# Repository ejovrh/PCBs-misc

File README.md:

# PCBs-misc
breakout stuff

breakout boards for all kinds of stull i currently need

- nikon d700 10-pin connector
- TPS63031 3.3v buck/boost dcdc converter
-

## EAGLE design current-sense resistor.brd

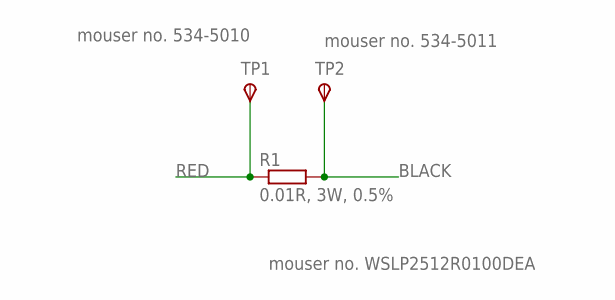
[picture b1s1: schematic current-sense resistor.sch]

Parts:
R1: 0.01R, 3W, 0.5%; R2512
TP1: 534-5011; P1-20
TP2: 534-5010; P1-20

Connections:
BLACK: R1.2, TP2.TP
RED: R1.1, TP1.TP

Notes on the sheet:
mouser no. 534-5011
mouser no. 534-5010
mouser no. WSLP2512R0100DEA

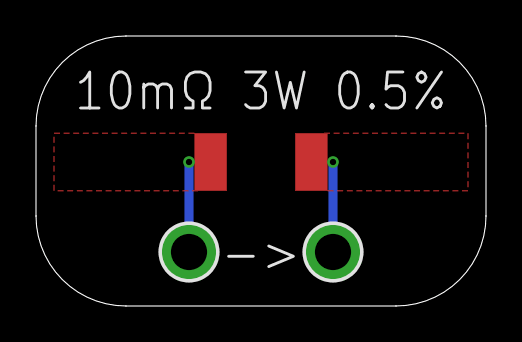
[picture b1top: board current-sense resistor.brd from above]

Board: 2 copper layers, 25.0 x 15.0 mm, 3 parts (0 on the bottom side), 2 nets.

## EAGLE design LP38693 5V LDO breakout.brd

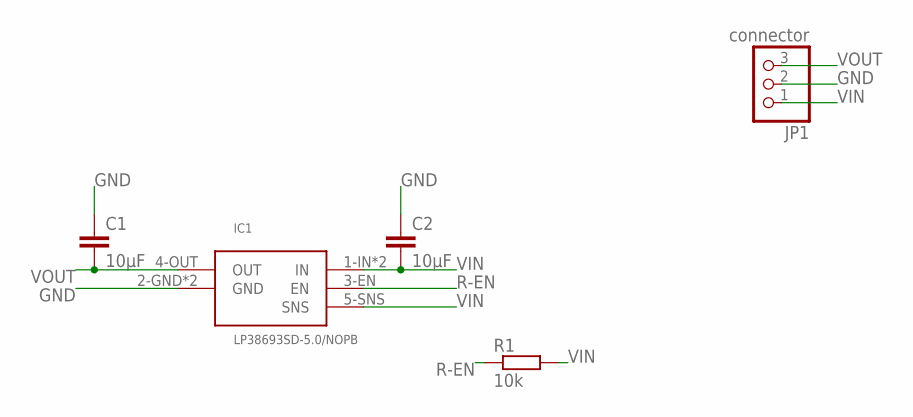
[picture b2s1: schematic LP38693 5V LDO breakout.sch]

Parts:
C1, C2: 10μF; C0402
IC1: LP38693SD-5.0/NOPB; WSON6
JP1: connector; 1X03
R1: 10k; R0402

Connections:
GND: C1.1, C2.1, IC1.2-GND (GND), IC1.GND1 (GND), JP1.2
R-EN: IC1.3-EN (EN), R1.1
VIN: C2.2, IC1.1-IN (IN), IC1.5-SNS (SNS), IC1.6-IN (IN), JP1.1, R1.2
VOUT: C1.2, IC1.4-OUT (OUT), JP1.3

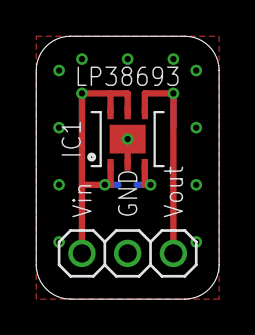
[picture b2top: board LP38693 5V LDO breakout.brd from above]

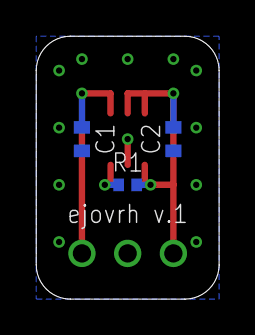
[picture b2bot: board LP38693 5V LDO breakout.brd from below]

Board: 2 copper layers, 10.2 x 14.6 mm, 5 parts (3 on the bottom side), 4 nets.

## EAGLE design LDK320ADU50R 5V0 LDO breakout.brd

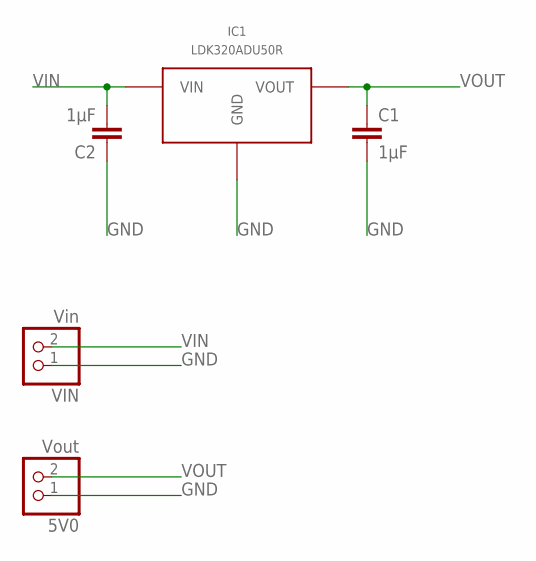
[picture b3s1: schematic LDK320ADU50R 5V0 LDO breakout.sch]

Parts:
5V0: Vout; 1X02
C1, C2: 1μF; C0402
IC1: LDK320ADU50R; SOT-89-D
VIN: Vin; 1X02

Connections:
GND: 5V0.1, C1.2, C2.1, IC1.GND, VIN.1
VIN: C2.2, IC1.VIN, VIN.2
VOUT: 5V0.2, C1.1, IC1.VOUT

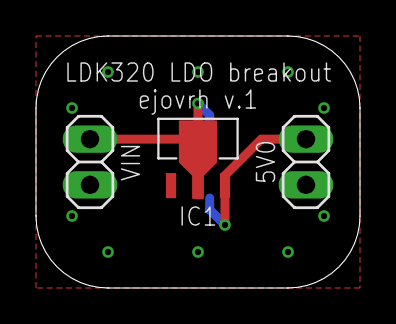
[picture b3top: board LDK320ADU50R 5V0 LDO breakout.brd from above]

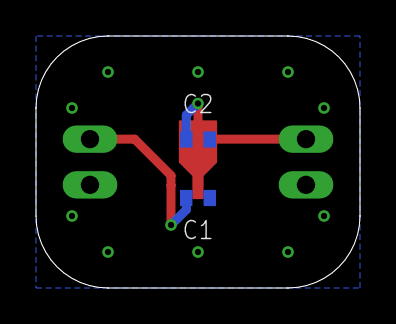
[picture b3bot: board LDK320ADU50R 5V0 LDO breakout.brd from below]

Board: 2 copper layers, 18.0 x 14.0 mm, 5 parts (2 on the bottom side), 3 nets.

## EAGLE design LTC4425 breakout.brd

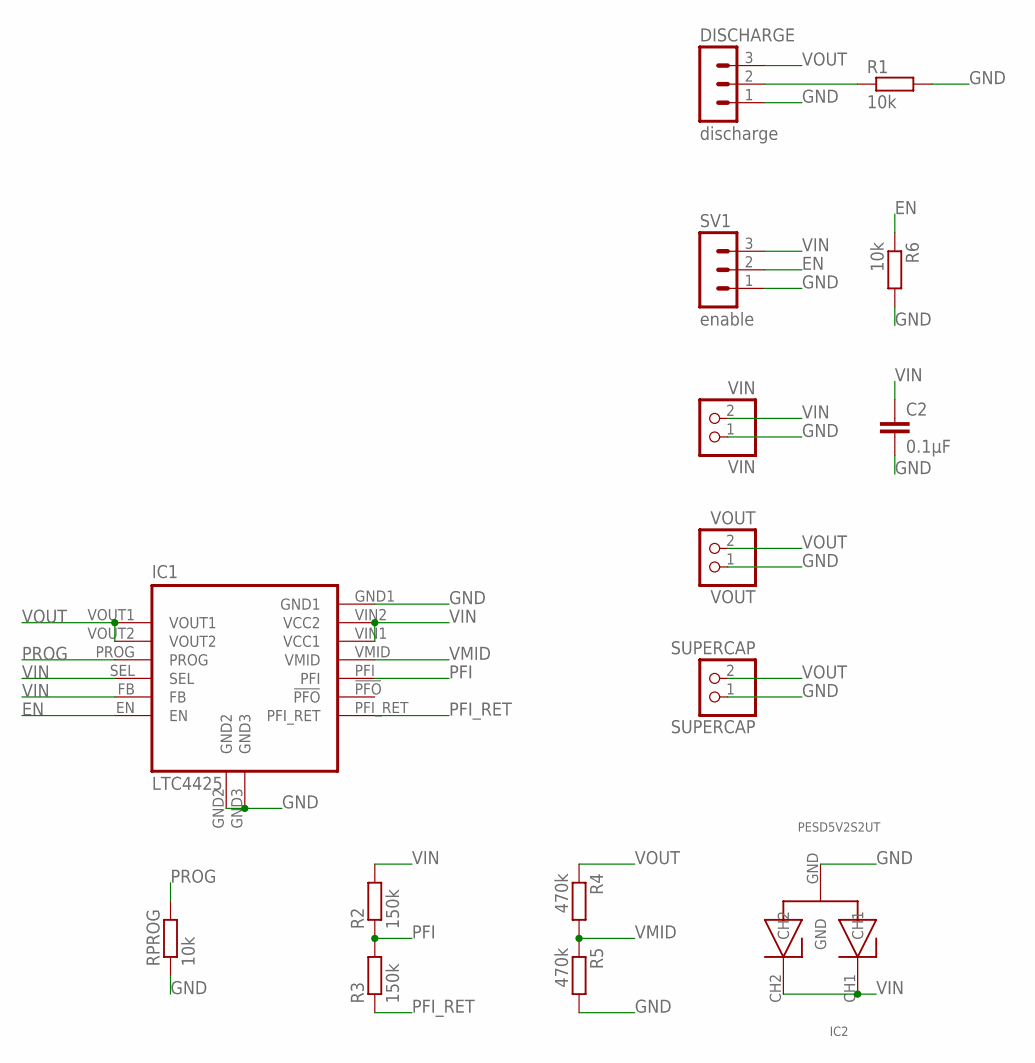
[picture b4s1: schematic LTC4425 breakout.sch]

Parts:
C2: 0.1µF; C0805
DISCHARGE: discharge; MA03-1
IC1: LTC4425; MSOP
IC2: PESD5V2S2UT; SOT-23
R1: 10k; R1206
R2, R3: 150k; R0805
R4, R5: 470k; R0805
R6: 10k; R0805
RPROG: 10k; R1206
SUPERCAP: SUPERCAP; 1X02
SV1: enable; MA03-1
VIN: VIN; 1X02
VOUT: VOUT; 1X02

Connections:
EN: IC1.EN, R6.1, SV1.2
GND: C2.2, DISCHARGE.1, IC1.GND1, IC1.GND2, IC1.GND3, IC2.GND, R1.2, R5.2, R6.2, RPROG.1, SUPERCAP.1, SV1.1, VIN.1, VOUT.1
unnamed: DISCHARGE.2, R1.1
PFI: IC1.PFI, R2.1, R3.2
PFI_RET: IC1.PFI_RET, R3.1
PROG: IC1.PROG, RPROG.2
VIN: C2.1, IC1.FB, IC1.SEL, IC1.VIN1 (VCC1), IC1.VIN2 (VCC2), IC2.CH1, IC2.CH2, R2.2, SV1.3, VIN.2
VMID: IC1.VMID, R4.2, R5.1
VOUT: DISCHARGE.3, IC1.VOUT1, IC1.VOUT2, R4.1, SUPERCAP.2, VOUT.2

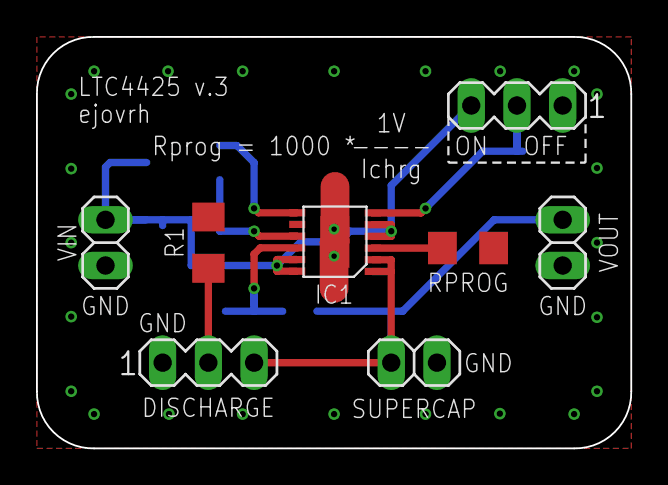
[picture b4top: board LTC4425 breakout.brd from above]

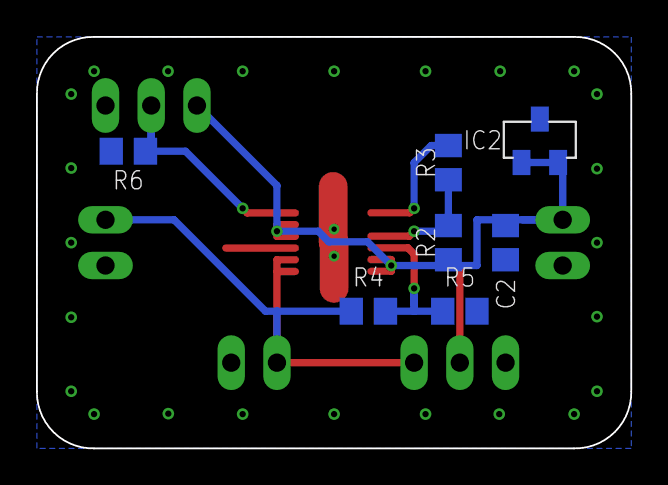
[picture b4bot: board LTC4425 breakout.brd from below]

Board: 2 copper layers, 33.0 x 22.9 mm, 15 parts (7 on the bottom side), 9 nets.

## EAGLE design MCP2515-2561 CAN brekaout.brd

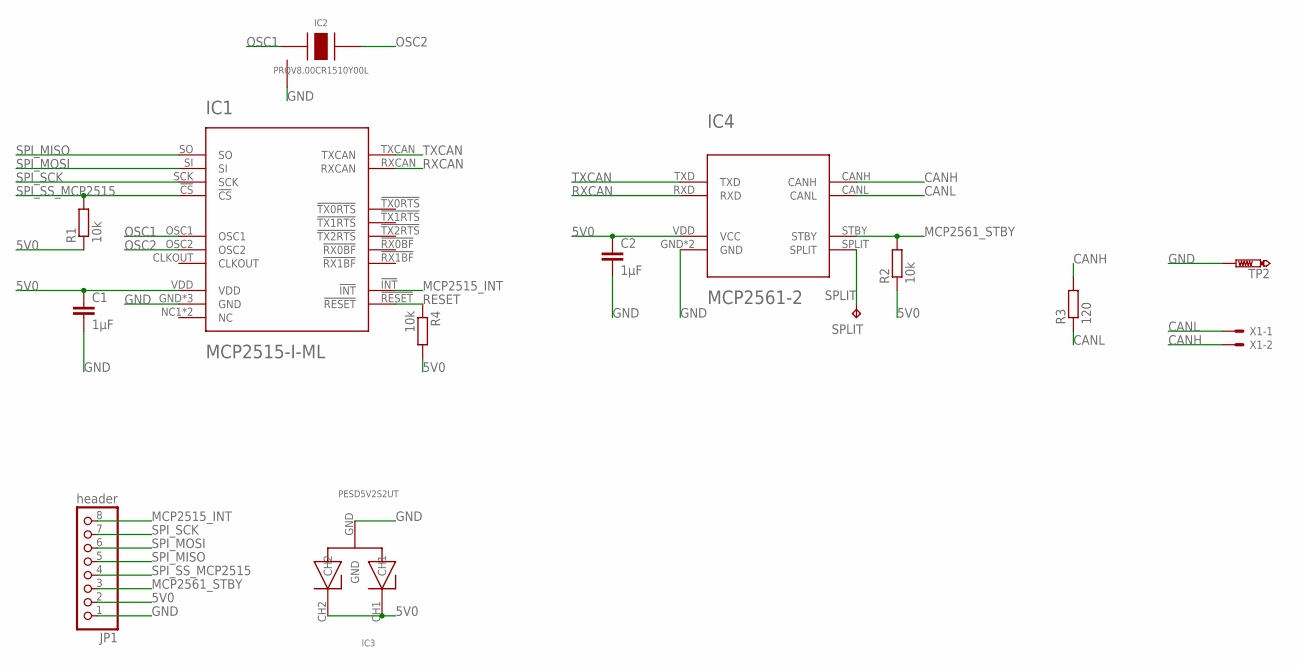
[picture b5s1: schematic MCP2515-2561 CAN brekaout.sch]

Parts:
C1, C2: 1μF; C0402
IC1: MCP2515-I-ML; QFN20
IC2: PRQV8.00CR1510Y00L; SMT
IC3: PESD5V2S2UT; SOT-23
IC4: MCP2561-2; DFN10
JP1: header; 1X08
R1, R2, R4: 10k; R0402
R3: 120; R0805
SPLIT: TPB2,54; B2,54
TP2: PTR1PAD1-13Y; P1-13Y
X1: 22-23-2021

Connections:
5V0: C1.1, C2.1, IC1.VDD, IC3.CH1, IC3.CH2, IC4.VDD (VCC), JP1.2, R1.1, R2.1, R4.2
CANH: IC4.CANH, R3.2, X1.2
CANL: IC4.CANL, R3.1, X1.1
GND: C1.2, C2.2, IC1.GND, IC1.GND1 (GND), IC1.GND6 (GND), IC2.GND, IC3.GND, IC4.GND, IC4.VSS (GND), JP1.1, TP2.TP
MCP2515_INT: IC1.!INT!, JP1.8
MCP2561_STBY: IC4.STBY, JP1.3, R2.2
OSC1: IC1.OSC1, IC2.XTAL1
OSC2: IC1.OSC2, IC2.XTAL2
RESET: IC1.!RESET!, R4.1
RXCAN: IC1.RXCAN, IC4.RXD
SPI_MISO: IC1.SO, JP1.5
SPI_MOSI: IC1.SI, JP1.6
SPI_SCK: IC1.SCK, JP1.7
SPI_SS_MCP2515: IC1.!CS!, JP1.4, R1.2
SPLIT: IC4.SPLIT, SPLIT.TP
TXCAN: IC1.TXCAN, IC4.TXD

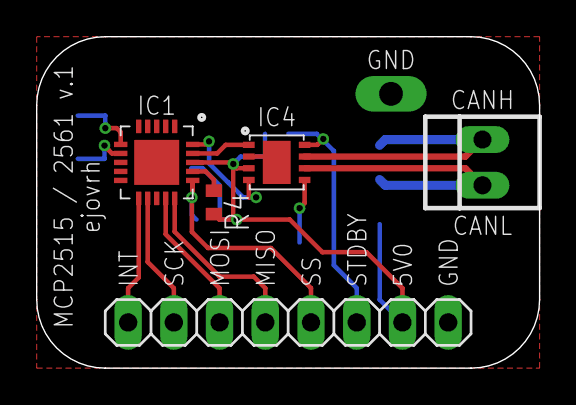
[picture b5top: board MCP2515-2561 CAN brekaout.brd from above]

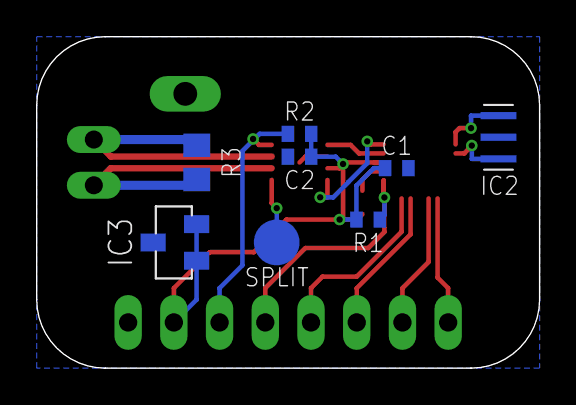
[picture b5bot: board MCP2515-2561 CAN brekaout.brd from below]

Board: 2 copper layers, 27.9 x 18.4 mm, 14 parts (8 on the bottom side), 16 nets.

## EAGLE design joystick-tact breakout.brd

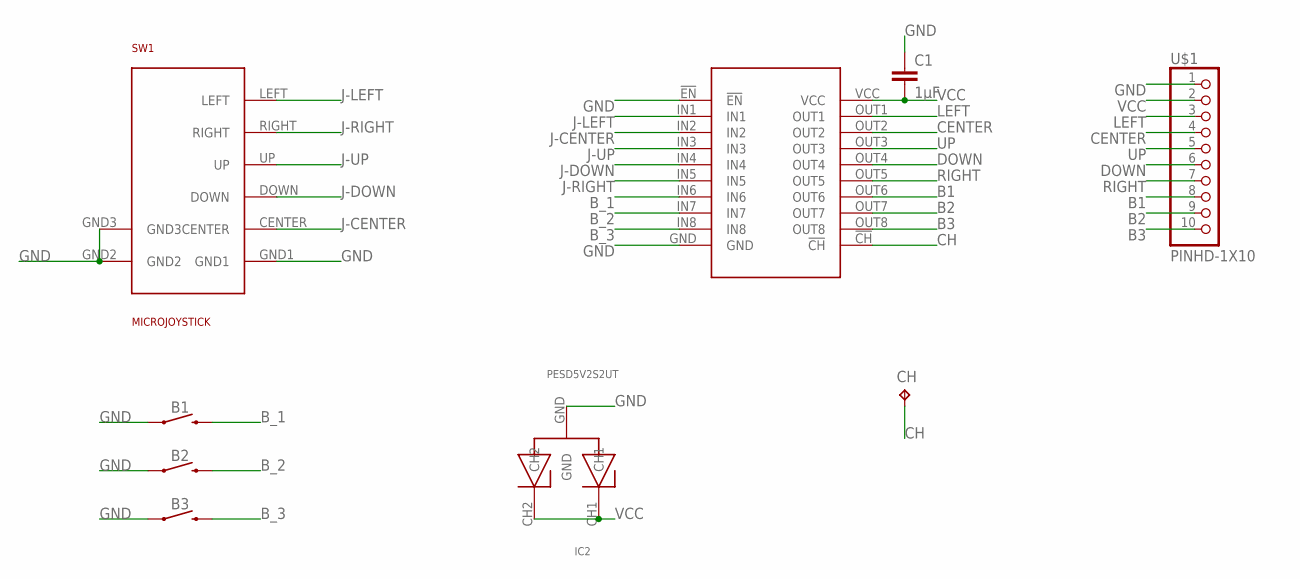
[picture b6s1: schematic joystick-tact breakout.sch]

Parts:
B1, B2, B3: MOMENTARY-SWITCH-SPST-SMD-4.5MM; TACTILE_SWITCH_SMD_4.5MM
C1: 1μF; C0805
CH: TPB2,54; B2,54
IC1: MAX6818; TSSOP20
IC2: PESD5V2S2UT; SOT-23
SW1: MICROJOYSTICK
U$1: PINHD-1X10; 1X10-BIG

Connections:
B1: IC1.OUT6, U$1.8
B2: IC1.OUT7, U$1.9
B3: IC1.OUT8, U$1.10
B_1: B1.1 (2), B1.4 (2), IC1.IN6
B_2: B2.1 (2), B2.4 (2), IC1.IN7
B_3: B3.1 (2), B3.4 (2), IC1.IN8
CENTER: IC1.OUT2, U$1.4
CH: CH.TP, IC1.!CH!
DOWN: IC1.OUT4, U$1.6
GND: B1.2 (1), B1.3 (1), B2.2 (1), B2.3 (1), B3.2 (1), B3.3 (1), C1.1, IC1.!EN!, IC1.GND, IC2.GND, SW1.GND1, SW1.GND2, SW1.GND3, U$1.1
J-CENTER: IC1.IN2, SW1.CENTER
J-DOWN: IC1.IN4, SW1.DOWN
J-LEFT: IC1.IN1, SW1.LEFT
J-RIGHT: IC1.IN5, SW1.RIGHT
J-UP: IC1.IN3, SW1.UP
LEFT: IC1.OUT1, U$1.3
RIGHT: IC1.OUT5, U$1.7
UP: IC1.OUT3, U$1.5
VCC: C1.2, IC1.VCC, IC2.CH1, IC2.CH2, U$1.2

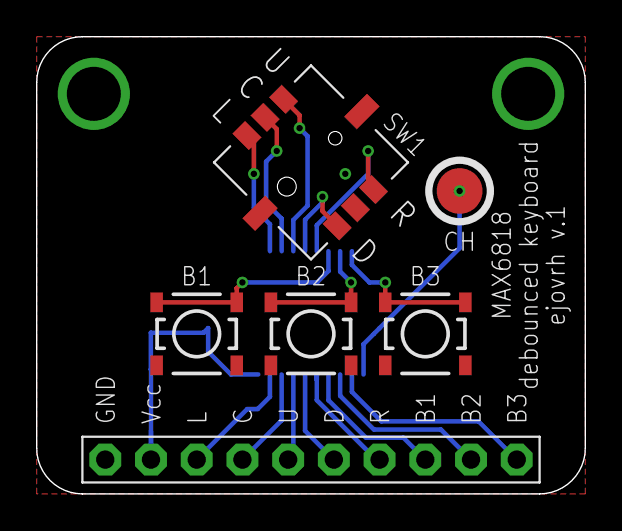
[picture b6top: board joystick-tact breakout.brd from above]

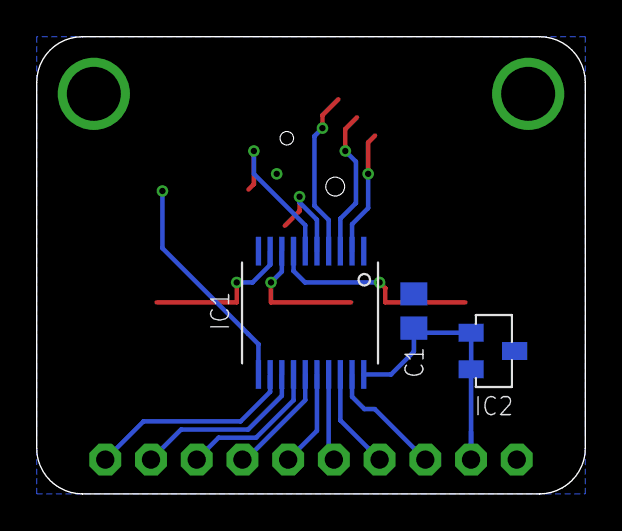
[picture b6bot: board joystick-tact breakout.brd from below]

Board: 2 copper layers, 30.5 x 25.4 mm, 9 parts (3 on the bottom side), 19 nets.

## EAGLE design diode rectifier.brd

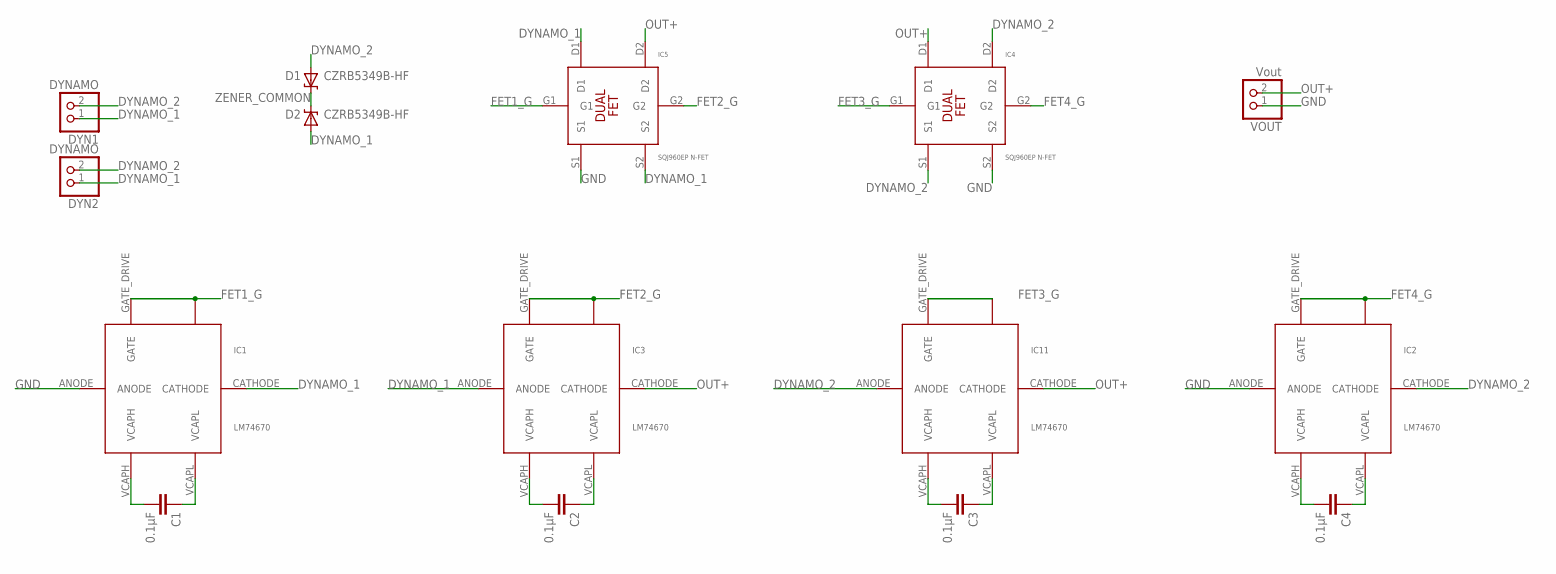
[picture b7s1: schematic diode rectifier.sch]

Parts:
C1, C2, C3, C4: 0.1μF; C0805
D1, D2: CZRB5349B-HF; DO-214
DYN1, DYN2: DYNAMO; 1X02
IC1, IC2, IC3, IC11: LM74670; VSSOP-8
IC4, IC5: SQJ960EP N-FET; SO-8L
VOUT: Vout; 1X02

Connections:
DYNAMO_1: D2.AN, DYN1.1, DYN2.1, IC1.CATHODE, IC3.ANODE, IC5.D1, IC5.S2
DYNAMO_2: D1.AN, DYN1.2, DYN2.2, IC2.CATHODE, IC4.D2, IC4.S1, IC11.ANODE
FET1_G: IC1.GATE_DRIVE (GATE), IC1.GATE_PULLD, IC5.G1
FET2_G: IC3.GATE_DRIVE (GATE), IC3.GATE_PULLD, IC5.G2
FET3_G: IC4.G1, IC11.GATE_DRIVE (GATE), IC11.GATE_PULLD
FET4_G: IC2.GATE_DRIVE (GATE), IC2.GATE_PULLD, IC4.G2
GND: IC1.ANODE, IC2.ANODE, IC4.S2, IC5.S1, VOUT.1
unnamed: C1.2, IC1.VCAPH
unnamed: C1.1, IC1.VCAPL
unnamed: C2.2, IC3.VCAPH
unnamed: C2.1, IC3.VCAPL
unnamed: C3.2, IC11.VCAPH
unnamed: C3.1, IC11.VCAPL
unnamed: C4.2, IC2.VCAPH
unnamed: C4.1, IC2.VCAPL
OUT+: IC3.CATHODE, IC4.D1, IC5.D2, IC11.CATHODE, VOUT.2
ZENER_COMMON: D1.CAT, D2.CAT

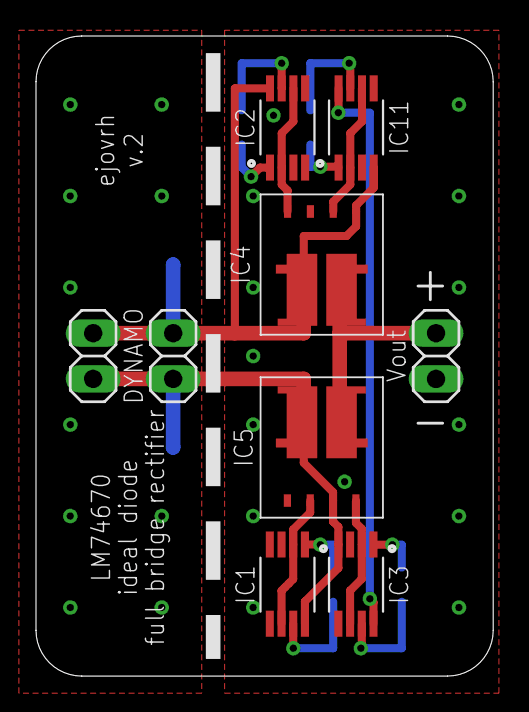
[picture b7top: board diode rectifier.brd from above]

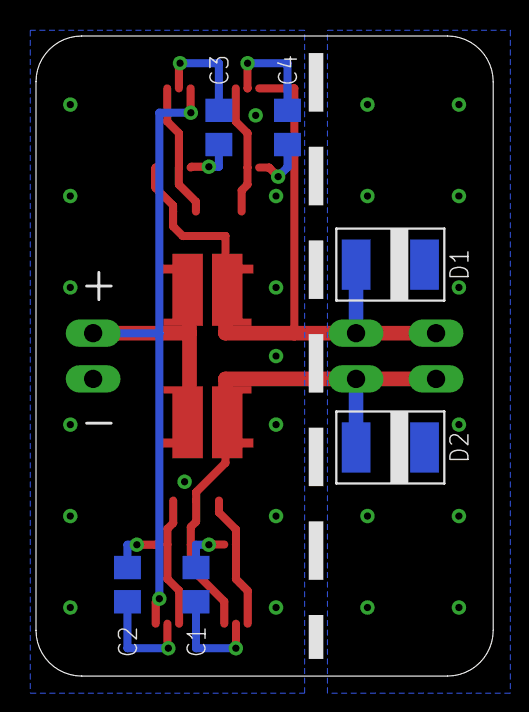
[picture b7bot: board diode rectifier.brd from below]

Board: 2 copper layers, 25.4 x 35.6 mm, 15 parts (6 on the bottom side), 17 nets.

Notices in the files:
parts and their libraries:
SparkFun-Switches: Licensing: Creative Commons ShareAlike 4.0 International - https://creativecommons.org/licenses/by-sa/4.0
